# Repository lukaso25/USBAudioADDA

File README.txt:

USB Audio ADDA Async
--------------------

This repository contains resources of USB audio interface based on TI microcontroller and Analog devices AD and DA converters. This interface use UAC 1 USB audio specifications, asynchronous clocking scheme. Interface is 24 b/ 96(88.2) kHz  capable in half-duplex mode and 24b / 44.1(48) kHz in full-duplex. 

Only 2 SW modules are relased yet because of unfriendly licencing of USB example code.

Link to pcb photo https://raw.githubusercontent.com/lukaso25/USBAudioADDA/master/photo%20prototype/03%20bottom.JPG

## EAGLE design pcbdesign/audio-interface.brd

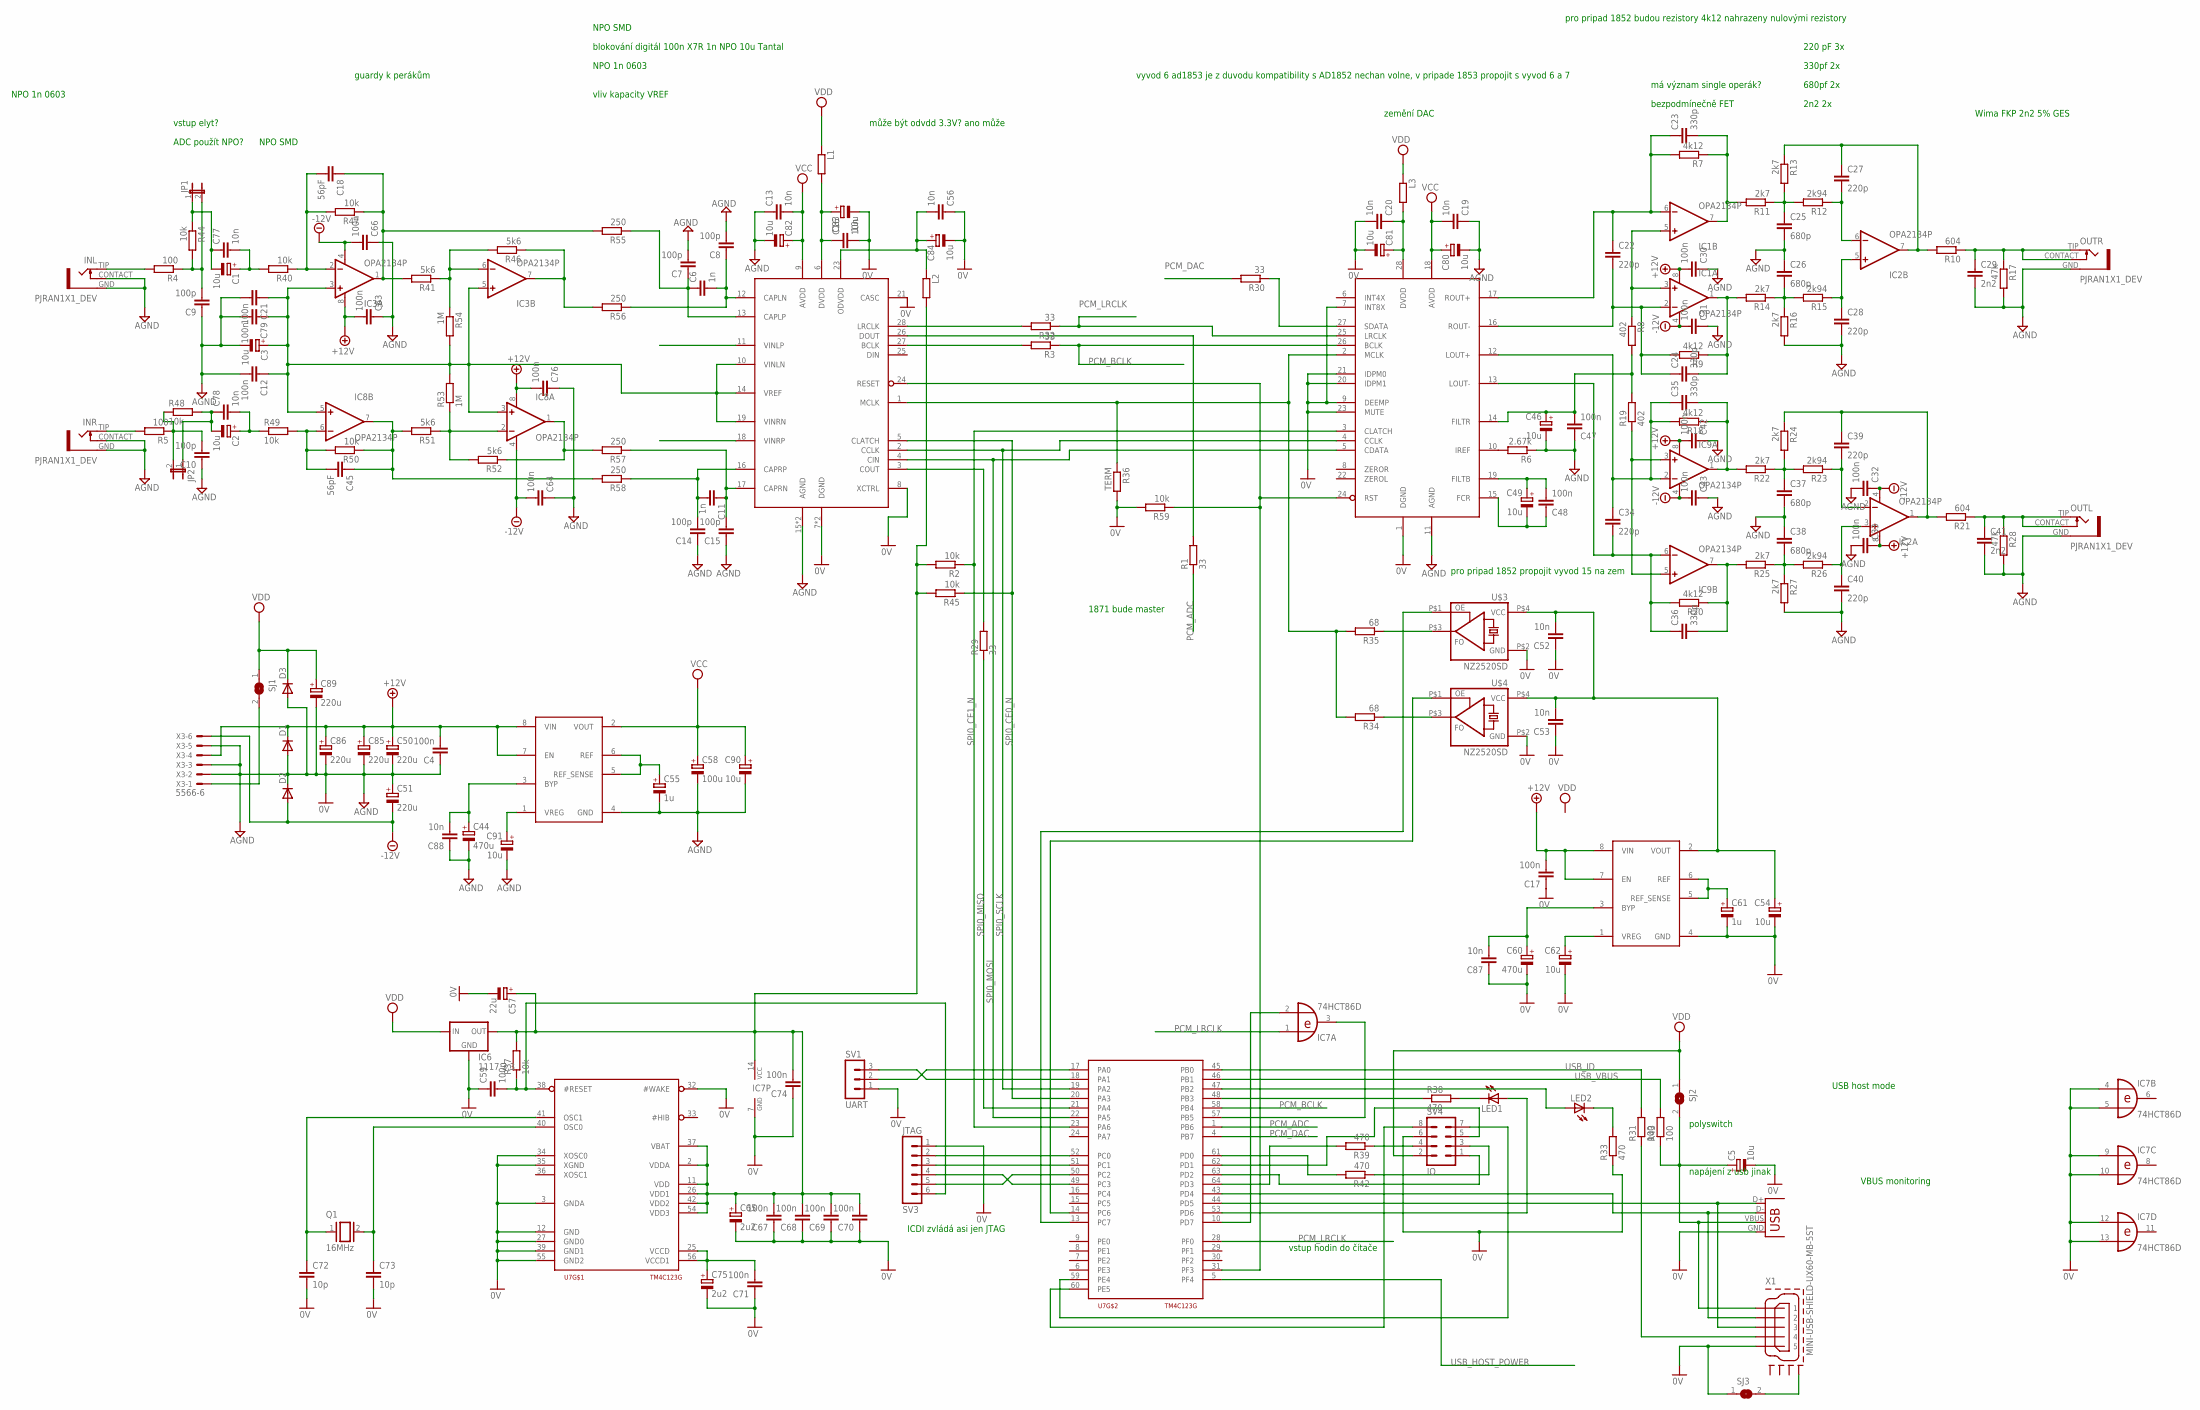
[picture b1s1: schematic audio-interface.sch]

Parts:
C1, C2: 10u; E2,5-5
C3, C5: 10u; E2,5-7
C4, C12, C17, C21, C30, C31, C32, C33, C42, C43, C47, C48, C59, C63, C64, C66, C67, C68, C69, C70, C71, C74, C76, C79: 100n; C0805
C6, C11: 1n; C0805K
C7, C8, C9, C10, C14, C15: 100p; C0805K
C13, C16, C19, C20, C52, C53, C56, C87, C88: 10n; C0805
C18, C45: 56pF; C0805K
C22, C27, C28, C34, C39, C40: 220p; C0805K
C23, C24, C35, C36: 330p; C0805K
C25, C26, C37, C38: 680p; C050-050X075
C29, C41: 2n2; C050-050X075
C44, C60: 470u; E2,5-7
C46, C49, C80, C81, C82, C83, C84: 10u; SMC_A
C50, C51, C85, C86, C89: 220u; E2,5-7
C54, C62, C90, C91: 10u; CT6032
C55, C61: 1u; CT3216
C57: 22u; CT6032
C58: 100u; E2,5-7
C65, C75: 2u2; CT3216
C72, C73: 10p; C0805
C77, C78: 10n; C0805K
D1, D2, D3: DIODE-MINIMELF; MINIMELF
IC1, IC3, IC8, IC9: OPA2134P; DIL08; MPN OPA2134PA
IC2: OPA2134P; DIL08
IC6: 1117 3.3; SOT223
IC7: 74HCT86D; SO14
INL: PJRAN1X1_DEV; PJRAN1X1
INR: PJRAN1X1_DEV; PJRAN1X1
JP1, JP2: JP1E; JP1
L1, L2, L3: R-EU_R0805; R0805
LED1, LED2: LED3MM
OUTL: PJRAN1X1_DEV; PJRAN1X1
OUTR: PJRAN1X1_DEV; PJRAN1X1
Q1: 16MHz; QS
R1, R3, R29, R30, R32: 33; R0805
R2, R37, R45, R59: 10k; R0805
R4, R5: 100; M0805
R6: 2.67k; M1406
R7, R9, R18, R20: 4k12; M1206
R8, R19: 402; M1206
R10, R21: 604; M1206
R11, R13, R14, R16, R22, R24, R25, R27: 2k7; M1206
R12, R15, R23, R26: 2k94; M1206
R17, R28: 47k; M1206
R31, R43: 100; R0805
R33, R38, R39, R42: 470; R0805
R34, R35: 68; M1206
R36: TERM; R0805
R40, R44, R47, R48, R49, R50: 10k; M1206
R41, R46, R51, R52: 5k6; M1206
R53, R54: 1M; M1206
R55, R56, R57, R58: 250; M1206
SJ1, SJ2, SJ3: SJ
SV1: UART; MA03-1
SV3: JTAG; MA06-1
SV4: IO; MA04-2
U1: AD1853; SSOP-28
U2: AD1871; SSOP-28
U5, U6: ADM7150; SO8-COOL
U7: TM4C123G; LQFP64
U$3, U$4: NZ2520SD; OSC2X2.5
X1: MINI-USB-SHIELD-UX60-MB-5ST; UX60-MB-5ST
X3: 5566-6
X7: USB-B-H

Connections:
+12V: C4.2, C17.2, C30.2, C33.1, C42.2, C50.+, C63.2, C76.2, C85.+, C86.+, D1.C, IC1.8 (V+), IC2.8 (V+), IC3.8 (V+), IC8.8 (V+), IC9.8 (V+), U5.7 (EN), U5.8 (VIN), U6.7 (EN), U6.8 (VIN), X3.4
-12V: C31.2, C32.1, C43.2, C51.-, C64.2, C66.2, D2.A, IC1.4 (V-), IC2.4 (V-), IC3.4 (V-), IC8.4 (V-), IC9.4 (V-), X3.6
AGND: C3.-, C4.1, C5.-, C7.2, C8.2, C9.1, C10.1, C12.2, C13.1, C14.1, C15.1, C16.2, C17.1, C19.1, C20.2, C21.2, C25.2, C26.1, C28.2, C29.2, C30.1, C31.1, C32.2, C33.2, C37.2, C38.1, C40.2, C41.2, C42.1, C43.1, C44.-, C46.-, C47.1, C50.-, C51.+, C52.1, C53.1, C54.-, C55.-, C56.1, C57.-, C58.-, C59.1, C60.-, C61.-, C62.-, C63.1, C64.1, C65.-, C66.1, C67.1, C68.1, C69.1, C70.1, C71.1, C72.2, C73.2, C74.1, C75.-, C76.1, C79.2, C80.-, C81.-, C82.-, C83.-, C84.-, C85.-, C86.-, C87.1, C88.1, C89.-, C90.-, C91.-, D1.A, D2.C, D3.A, IC6.1 (GND), IC7.4 (I0), IC7.5 (I1), IC7.7 (GND), IC7.9 (I0), IC7.10 (I1), IC7.12 (I0), IC7.13 (I1), INL.CONTACT (SWITCH), INL.GND, INR.CONTACT (SWITCH), INR.GND, OUTL.GND, OUTR.GND, R6.1, R16.2, R17.2, R27.2, R28.2, R33.1, R36.2, R59.2, SJ3.1, SV1.1, SV3.1, SV4.6, U1.1 (DGND), U1.7 (INT8X), U1.9 (DEEMP), U1.11 (AGND), U1.20 (IDPM1), U1.21 (IDPM0), U1.23 (MUTE), U2.7 (DGND), U2.8 (XCTRL), U2.15 (AGND), U2.20 (AGND), U2.21 (CASC), U2.22 (DGND), U5.4 (GND), U6.4 (GND), U7.3 (GNDA), U7.12 (GND), U7.27 (GND0), U7.32 (#WAKE), U7.34 (XOSC0), U7.35 (XGND), U7.39 (GND1), U7.55 (GND2), U$3.P$2 (GND), U$4.P$2 (GND), X1.5, X3.2, X3.3, X3.5, X7.GND
unnamed: R59.1, U1.24 (RST), U2.24 (RESET), U7.31 (PF3)
unnamed: R35.1, U$3.P$3 (FO)
unnamed: R32.2, U2.28 (LRCLK)
unnamed: IC7.3 (O), U7.57 (PB5)
unnamed: R1.2, U2.26 (DOUT)
unnamed: C55.+, U5.5 (REF_SENSE), U5.6 (REF)
unnamed: C91.+, U5.1 (VREG)
unnamed: C44.+, C88.2, U5.3 (BYP)
unnamed: R34.2, R35.2, R36.1, U1.2 (MCLK), U2.1 (MCLK)
unnamed: C6.2, C8.1, R56.1, U2.12 (CAPLN)
unnamed: R29.2, U2.3 (COUT)
unnamed: C60.+, C87.2, U6.3 (BYP)
unnamed: C62.+, U6.1 (VREG)
unnamed: C61.+, U6.5 (REF_SENSE), U6.6 (REF)
unnamed: C1.+, C77.2, R40.2
unnamed: IC3.7 (OUT), R46.1, R56.2
unnamed: C71.2, C75.+, U7.25 (VCCD), U7.56 (VCCD1)
unnamed: C22.2, C24.1, IC1.2 (-IN), R9.2, U1.16 (ROUT-)
unnamed: C6.1, C7.1, R55.1, U2.13 (CAPLP)
unnamed: C45.1, IC8.7 (OUT), R50.1, R51.2, R58.2
unnamed: C11.1, C15.2, R57.1, U2.17 (CAPRN)
unnamed: C22.1, C23.1, IC1.6 (-IN), R7.2, U1.17 (ROUT+)
unnamed: SV1.3, U7.18 (PA1)
unnamed: IC8.1 (OUT), R52.1, R57.2
unnamed: C24.2, IC1.1 (OUT), R9.1, R14.2
unnamed: C11.2, C14.2, R58.1, U2.16 (CAPRP)
unnamed: IC8.2 (-IN), R51.1, R52.2, R53.1
unnamed: IC3.6 (-IN), R41.1, R46.2, R54.1
unnamed: C3.+, C12.1, C21.1, C79.1, IC3.3 (+IN), IC3.5 (+IN), IC8.3 (+IN), IC8.5 (+IN), R53.2, R54.2, U2.10 (VINLN), U2.14 (VREF), U2.19 (VINRN)
unnamed: C23.2, IC1.7 (OUT), R7.1, R11.2
unnamed: C46.+, C47.2, R8.2, R19.2, U1.14 (FILTR)
unnamed: C26.2, R14.1, R15.2, R16.1
unnamed: R6.2, U1.10 (IREF)
unnamed: C25.1, R11.1, R12.2, R13.2
unnamed: C27.2, IC2.6 (-IN), R12.1
unnamed: C28.1, IC2.5 (+IN), R15.1
unnamed: C27.1, IC2.7 (OUT), R10.2, R13.1
unnamed: C48.2, C49.+, U1.19 (FILTB)
unnamed: C29.1, OUTR.CONTACT (SWITCH), OUTR.TIP (HOT), R10.1, R17.1
unnamed: C48.1, C49.-, U1.15 (FCR)
unnamed: SV3.5, U7.50 (PC2)
unnamed: C34.2, C36.1, IC9.6 (-IN), R20.2, U1.13 (LOUT-)
unnamed: C36.2, IC9.7 (OUT), R20.1, R25.2
unnamed: IC9.3 (+IN), IC9.5 (+IN), R19.1
unnamed: C35.2, IC9.1 (OUT), R18.1, R22.2
unnamed: C38.2, R25.1, R26.2, R27.1
unnamed: C37.1, R22.1, R23.2, R24.2
unnamed: C39.2, IC2.2 (-IN), R23.1
unnamed: C40.1, IC2.3 (+IN), R26.1
unnamed: C39.1, IC2.1 (OUT), R21.2, R24.1
unnamed: R3.2, U2.27 (BCLK)
unnamed: IC1.3 (+IN), IC1.5 (+IN), R8.1
unnamed: C18.1, IC3.1 (OUT), R41.2, R47.1, R55.2
unnamed: INR.TIP (HOT), R5.2
unnamed: C10.2, JP2.2, R5.1, R48.1
unnamed: R34.1, U$4.P$3 (FO)
unnamed: C34.1, C35.1, IC9.2 (-IN), R18.2, U1.12 (LOUT+)
unnamed: C2.+, C78.2, R49.1
unnamed: C72.1, Q1.1, U7.41 (OSC1)
unnamed: C52.2, C53.2, C54.+, U6.2 (VOUT), U$3.P$4 (VCC), U$4.P$4 (VCC)
unnamed: C45.2, IC8.6 (-IN), R49.2, R50.2
unnamed: C73.1, Q1.2, U7.40 (OSC0)
unnamed: SV4.1, U7.63 (PD2)
unnamed: SV1.2, U7.17 (PA0)
unnamed: R39.2, U7.64 (PD3)
unnamed: SV3.4, U7.49 (PC3)
unnamed: LED1.A, U7.53 (PD6)
unnamed: C18.2, IC3.2 (-IN), R40.1, R47.2
unnamed: C9.2, JP1.2, R4.1, R44.2
unnamed: INL.TIP (HOT), R4.2
unnamed: U7.44 (PD5), X1.3, X7.D+
unnamed: U7.43 (PD4), X1.2, X7.D-
unnamed: C59.2, R37.1, SV3.6, U7.38 (#RESET)
unnamed: SV3.2, U7.52 (PC0)
unnamed: SV3.3, U7.51 (PC1)
unnamed: IC7.2 (I1), U7.10 (PD7)
unnamed: LED2.K (C), R33.2
unnamed: LED1.K (C), R38.2
unnamed: U7.14 (PC6), U$4.P$1 (OE)
unnamed: U7.13 (PC7), U$3.P$1 (OE)
unnamed: R42.2, U7.61 (PD0)
unnamed: C16.1, C83.+, L1.2, U2.6 (DVDD)
unnamed: C56.2, C84.+, L2.1, U2.23 (ODVDD)
unnamed: R38.1, U7.48 (PB3)
unnamed: C57.+, C65.+, C67.2, C68.2, C69.2, C70.2, C74.2, IC6.2 (OUT), IC7.14 (VCC), L2.2, R2.2, R37.2, R45.2, U7.2 (VDDA), U7.11 (VDD), U7.26 (VDD1), U7.37 (VBAT), U7.42 (VDD2), U7.54 (VDD3)
unnamed: R30.1, U1.27 (SDATA)
unnamed: R39.1, SV4.4
unnamed: SV4.8, U7.60 (PE5)
unnamed: SV4.5, U7.62 (PD1)
unnamed: R42.1, SV4.3
unnamed: SV4.7, U7.59 (PE4)
unnamed: C1.-, C77.1, JP1.1, R44.1
unnamed: C2.-, C78.1, JP2.1, R48.2
unnamed: LED2.A, U7.47 (PB2)
unnamed: C20.1, C81.+, L3.2, U1.28 (DVDD)
unnamed: SJ1.2, X3.1
unnamed: C5.+, R43.1, SJ2.2, X1.1, X7.VBUS
unnamed: R31.1, X1.4
unnamed: SJ3.2, X1.M4 (GND4)
OUTL: C41.1, OUTL.CONTACT (SWITCH), OUTL.TIP (HOT), R21.1, R28.1
PCM_ADC: R1.1, U7.1 (PB6)
PCM_BCLK: R3.1, U1.26 (BCLK), U7.58 (PB4)
PCM_DAC: R30.2, U7.4 (PB7)
PCM_LRCLK: IC7.1 (I0), R32.1, U1.25 (LRCLK), U7.28 (PF0)
SPI0_CE0_N: R45.1, U2.5 (CLATCH), U7.20 (PA3)
SPI0_CE1_N: R2.1, U1.3 (CLATCH), U7.23 (PA6)
SPI0_MISO: R29.1, U7.21 (PA4)
SPI0_MOSI: U1.5 (CDATA), U2.4 (CIN), U7.22 (PA5)
SPI0_SCLK: U1.4 (CCLK), U2.2 (CCLK), U7.19 (PA2)
USB_HOST_POWER: U7.5 (PF4)
USB_ID: R31.2, U7.45 (PB0)
USB_VBUS: R43.2, U7.46 (PB1)
VCC: C13.2, C19.2, C58.+, C80.+, C82.+, C90.+, U1.18 (AVDD), U2.9 (AVDD), U5.2 (VOUT)
VDD: C89.+, D3.C, IC6.3 (IN), L1.1, L3.1, SJ1.1, SJ2.1, SV4.2

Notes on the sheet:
1871 bude master
bezpodmínečně FET
může být odvdd 3.3V? ano může
ICDI zvládá asi jen JTAG
USB host mode
vstup elyt?
ADC použít NPO?
NPO SMD
blokování digitál 100n X7R 1n NPO 10u Tantal
NPO 1n 0603
vliv kapacity VREF
zemění DAC
220 pF 3x
330pf 2x
680pf 2x
2n2 2x
má význam single operák?
Wima FKP 2n2 5% GES
vstup hodin do čítače
napájení z usb jinak
VBUS monitoring
guardy k perákům
polyswitch
vyvod 6 ad1853 je z duvodu kompatibility s AD1852 nechan volne, v pripade 1853 propojit s vyvod 6 a 7
pro pripad 1852 propojit vyvod 15 na zem
pro pripad 1852 budou rezistory 4k12 nahrazeny nulovými rezistory

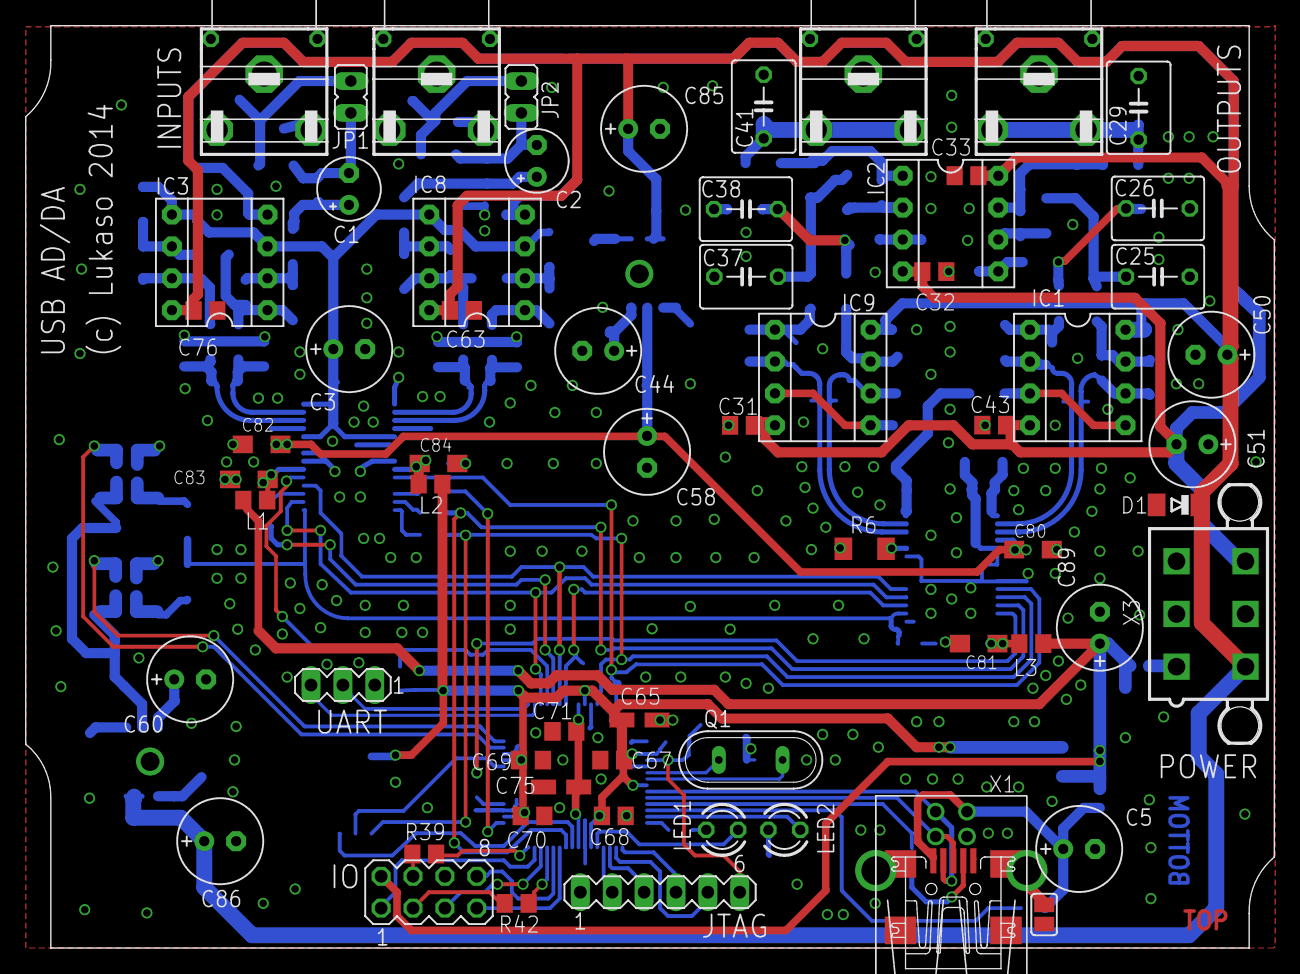
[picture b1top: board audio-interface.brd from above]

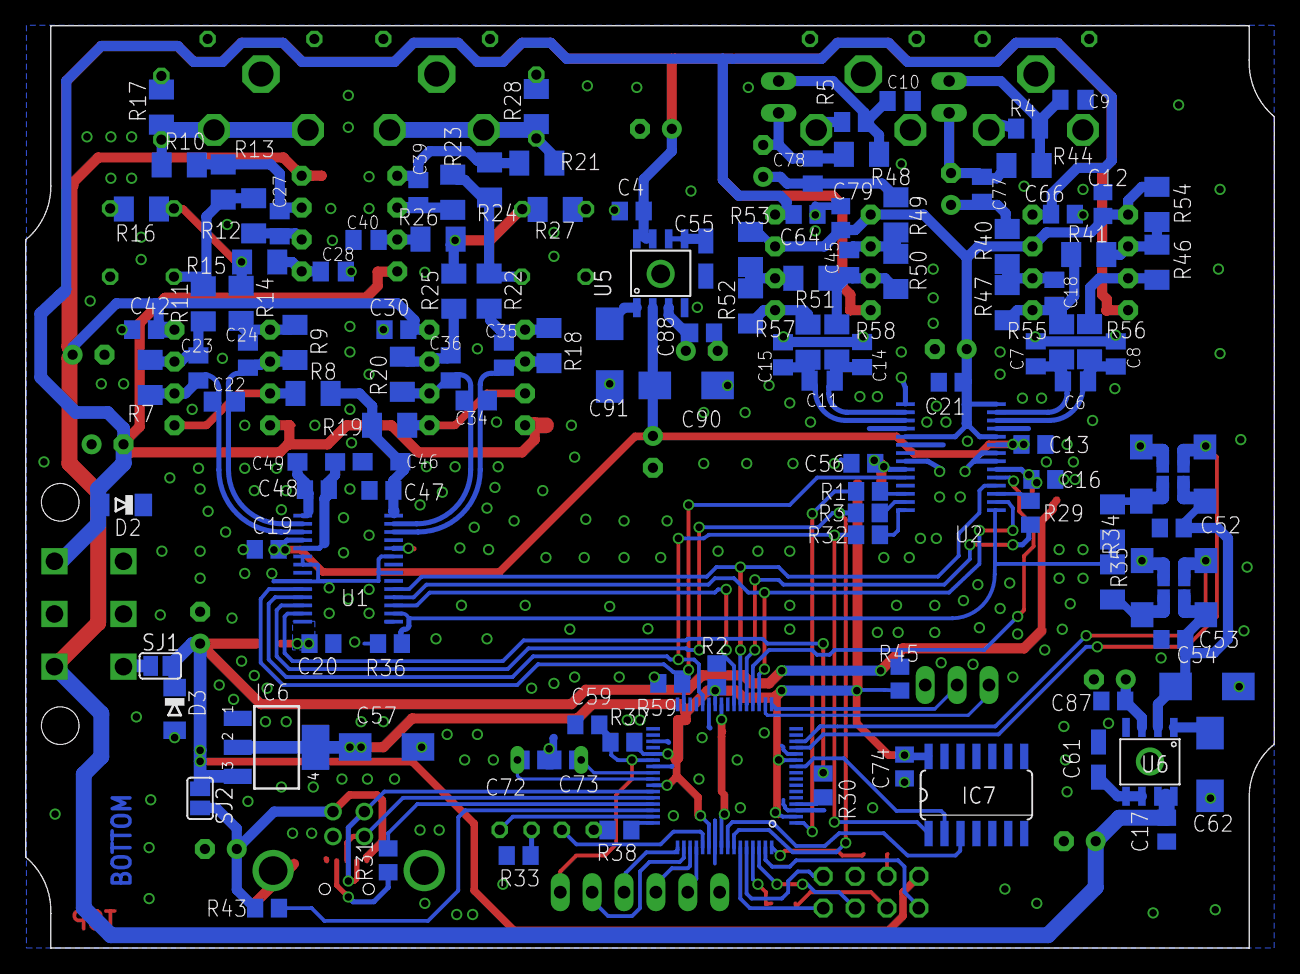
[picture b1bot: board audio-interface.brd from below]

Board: 2 copper layers, 99.5 x 73.5 mm, 188 parts (124 on the bottom side), 116 nets.

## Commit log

2015-01-09 initial commit with HW files
2015-01-09 readme commit
2015-01-25 ADC DAC code update, volume look-up tables
    Added code related to ADC and DAC; Added documentation - volume look-up
    table
2015-02-17 Updated documentation to modules
2015-02-18 documentary photo uploaded
2015-03-11 bitmap schematics
2015-03-11 Readme updated, prototype photoes uploaded
2015-03-12 measuremnt results
2015-10-02 photo link added
2016-02-03 loopup modified
